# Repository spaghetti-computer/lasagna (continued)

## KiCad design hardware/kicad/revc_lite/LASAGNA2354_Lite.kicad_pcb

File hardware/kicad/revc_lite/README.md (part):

# LASAGNA LITE (WeAct RP2350B), PRE-ROUTE proposal

> **Current configuration (2026-10-17, supersedes everything below).** The Waveshare Core2350B is replaced by the
> **WeAct Studio RP2350B Core Board V1.0** (41.148 x 41.402 mm, two 2x15 2.54 mm headers, rows 38.10 mm apart, own USB-C
> with CC resistors + TVS, BOOT/RST buttons, 16 MB flash). Board stays **100 x 67 mm**. Sections after this one are history
> (Waveshare era) and are kept for reference only. Regenerate with:
>
> `cd ../revc && LASAGNA_LITE=1 python3 gen_sch.py && LASAGNA_LITE=1 python3 gen_pcb.py && LASAGNA_LITE=1 python3 export_fab.py`

## Module (verified against WeActStudio.RP2350BCoreBoard HDK: RP2350B_SCH.pdf H1/H2, RP2350B_PINOUT.png, dimension drawing)
- Footprint `NESPICO_RevC:WeAct_RP2350B_CoreBoard` (generated by `gen_pcb.py` from `design.weact_pins()`): pad 1xx = H1 pin xx, 2xx = H2 pin xx.
  Origin = module centre, +y = USB-C edge. Pin 1/2 row 1.778 mm from the USB edge, far edge 4.064 mm past pin 29/30, rows 38.10 mm (outer) / 33.02 mm (inner) apart.
  The community footprints (fp_leomanes, fp_bwally0) were only used as a cross-check (leomanes agrees within 0.1 mm; bwally0 uses a different pad numbering).
- Placement: module centre (50.00, 46.30), x 29.43-70.57, y 25.60-67.00, **USB-C flush with the front edge**. H2 (GP25-47) on the left, H1 (GP0-24) on the right (top view).
- **H1:** 1 VBUS (raw USB), 2 +5V (after the module diode U2), 3/4 GND, 5 VREF, pin k = GP(k-6) for k = 6..30. Odd = outer row.
- **H2:** 1/2/4 GND, 3 3V3_EN, 5/6 3V3, 7 GP47, 8 RUN, 9 GP45, 10 GP46, 11 GP43, 12 GP44, ... 29 GP25, 30 GP26. Even = outer row.
- **Power:** +5V_LOGIC = **H1-1 VBUS** -> F1 PTC (JP2 bypass, open) -> VBUS_F -> JP1 bridged (D2 SS34 DNP) -> +5V_LOGIC.
  **H1-2 is NOT used**: the module diode drop could take the AHCT supply below 4.5 V. +3V3 = module LDO on H2-5/6.
  Not connected: H1-2 +5V, H1-5 VREF, H2-3 3V3_EN, H2-8 RUN.
- **Module handling (also on the front silk next to the module):**
  - **Lift module R16** (GP23 -> KEY button with a 5.1k pull-up to 3V3). GP23 carries OE#; with R16 fitted a KEY press would enable the AHCT outputs.
  - **Never fit the PSRAM/flash2 footprint U7** on the module bottom (its CS is GP0 = PPU AD0, through R14 0R with R13 10k to 3V3).
  - GP25 (CPU AD0, MCU side of RN1) drives the module LED through 5.1k: harmless (about 0.3 mA), the LED blinks with bus activity.
  - Newer WeAct lots ship RP2350B0**A4** (E9 fixed); R41 (5.1k CIRAM_A10 pull-down) stays fitted anyway (harmless on A4, required on A2).
- Solder the module on the supplied 2x15 male headers (do not fit pins pointing down on its 1x4 SWD header). Only bare THT test pads sit under the module.

## GPIO map (firmware swap, approved 2026-10-17)
| GPIO | Net | Function | Header pin |
|---|---|---|---|
| 0-7 | PADM0-7 | PPU AD0-7 (via RN3/RN4 33R) | H1-6..13 |
| 8-13 | GPA8-13 | PPU A8-13 -> U7 (GPA13 also U8) | H1-14..19 |
| 14 | PPU_DEN_N | U5 245 /OE (R32 10k to 3V3) | H1-20 |
| 15 | G_RD | -> U8 -> CART_RD_N | H1-21 |
| 16 | G_WR_N | U5 DIR, U7 -> CART_WR_N | H1-22 |
| 17 | PPU_ALE | U3 573 LE | H1-23 |
| 18 / 19 / 20 | CVBS_B0 / B1 / B2 | CVBS DAC R90 910 / R91 470 / R92 220 (DNP), 3V3-only | H1-24 / 25 / 26 |
| 21 | IRQ_N | cart pin 15 (R39 10k to 3V3), 5V-tolerant pin | H1-27 |
| 22 | CIRAM_CE_N | cart pin 48, 5V-tolerant pin | H1-28 |
| 23 | OUT_OE_N | OE# of all 7 AHCT (R30 10k to 3V3), 3V3-only. Module KEY pin: **lift R16** | H1-29 |
| 24 | CIRAM_A10 | cart pin 18, **R41 5.1k pull-down** (E9), 5V-tolerant pin | H1-30 |
| 25-32 | CADM0-7 | CPU AD0-7 (via RN1/RN2 33R) | H2-29,30,27,28,25,26,23,24 |
| 33-39 | GA8-14 | CPU A8-14 -> U6 | H2-21,22,19,20,17,18,15 |
| 40 | G_RW | U4 DIR, U6 -> CART_RW | H2-16 |
| 41 | G_ROMSEL_N | U7 -> CART_ROMSEL_N | H2-13 |
| 42 | G_M2_N | U4 /OE, U8 -> M2 (R31 10k to 3V3) | H2-14 |
| 43 | CPU_ALE | U2 573 LE | H2-11 |
| 44 / 45 | I2C_SDA / I2C_SCL | U10 MCP23017, J9 Grove (DNP), 4.7k to 3V3 | H2-12 / H2-9 |
| 46 | SPARE_GP46 | audio PWM (R60, DNP), J10 EXP, TP G46 | H2-10 |
| 47 | SPARE_GP47 | J10 EXP, TP G47 | H2-7 |

- **PIO window rule:** the PPU group (GP0-17) sits inside GPIO0-31 and the CPU group (GP25-43) inside GPIO16-47 (tested).
- **GPIO40-47 rule:** these are the ADC pads and are **not 5 V tolerant**. Every net on GPIO40-47 may only reach an AHCT input
  (573 LE/D, 541/540 A/OE, 245 DIR/OE) or a 3.3 V-only part (MCP23017, Grove, EXP header, 3V3 pull-ups). Never a 245 A/B pin, the cart slot,
  or a pull-up to +5V. `tests/test_lite.py::test_gpio40_47_only_drive_ahct_inputs_or_3v3_parts` enforces it with **zero exceptions**.
  R63 (GPIO46 -> cart pin 45) was deleted 2026-10-17; cart pin 45 (audio from 2A03) is NC again, pin 31 NC (pin 30 = +5V).
  R62 (cart pin 46 -> audio filter, DNP) stays: it only feeds the RC node, never a GPIO directly.
- Firmware order unchanged: set 245 DIR (G_RW / G_WR_N) and the bus levels, then pull the 245 /OE (G_M2_N / PPU_DEN_N) and OE# (GPIO23) low;
  release OE before changing DIR.
- **Lite pin swaps (firmware-invisible):** U2/U3 573 latches carry bit 7-j on D/Q pair j, and each RN 33R array carries bit b0+3-e on element e,
  so the module -> RN -> 573/245 -> slot buses run without crossings.

## Parts changed vs the Waveshare Lite
- **Removed:** J1 Akizuki USB-C breakout, R5/R6 CC 5.1k, U12 USBLC6-2SC6 (the module has USB-C, CC and TVS), SW1/SW2 (module has BOOT/RST),
  TP SWC/SWD/BT/RUN, the "DO NOT USE MODULE FPC" silk. The 22nd TP is GND again.
- **Changed:** U1 = WeAct RP2350B (60 pins, new symbol/footprint, courtyard 41.65 x 41.65 mm, silk on 3 sides, fab marks for the RP2350B, PSRAM U7, SWD 1x4 and USB-C shell legs).
  F1 now fed from H1-1 VBUS. GPIO map as above. R41 moved with CIRAM_A10 (GP24).
- **Kept:** F1 PTC (fitted) + JP2 (open), D2 SS34 DNP + JP1 bridged, R30/R31/R32/R39 pull-ups to 3V3, R41 5.1k fitted, all DNP options
  (MCP23017 + J4/J5, Grove J9 Seeed order, CVBS + J6, audio chain + J11, J10 EXP).

## Placement (mm, board origin top-left, y down; all key parts locked)
| Part | Position | Note |
|---|---|---|
| J3 cart slot | pin 1 (13.17, 7.80) | top edge, CPU pins left, PPU right |
| Row A, y = 18.0, 13 mm pitch | U6 11.0 (90), U2 24.0 (90), U4 37.0 (270), U8 50.0 (90), U7 63.0 (90), U3 76.0 (90), U5 89.0 (270) | inputs face the module, outputs face the slot (245 A side up) |
| 100 nF | C14 (8.08,12.54) C10 (21.08,12.54) C12 (39.93,23.46) C16 (47.07,12.54) C15 (60.07,12.54) C11 (73.07,12.54) C13 (91.93,23.46) | 2.6 mm from each VCC pin 20 |
| Pull-ups in row-A gaps | R31 (42.3,18) R30 (44.7,18) R39 (55.3,18) R41 (57.7,18) R32 (69.5,18) | on G_M2_N / OE# / IRQ / A10 / DEN |
| U1 WeAct | centre (50.00, 46.30) | USB-C flush with y = 67 |
| RN1 / RN2 | (26.4, 31.0) / (26.4, 36.0), 180 deg | left of H2 GP25-32 |
| RN3 / RN4 | (73.6, 57.1) / (73.6, 52.5), 0 deg | right of H1 GP0-7 |
| F1 / JP2 / D2 / JP1 / C1 | (74.6,64.8) / (74.6,61.6) / (80.6,64.8) / (80.6,61.6) / (86.0,64.8) | next to H1-1 VBUS, two aligned columns + C1 on the same row |
| TP1-22 | 3 rows (y 27.0 / 30.9 / 34.8) x 8, 3.2 mm pitch, centred x = 48.5 | bare THT pads under the module's far end, labels on B.Silk |
| CVBS / audio passives | R90/R91/R92 (80.4/82.0/84.0, 35.0); R60/C60/C61 (same x, 45.0); R61/R62 (80.4/82.0, 50.0) | one column grid per RCA |
| Options | J6 (93.1,33) J11 (93.1,49) right edge; J9 (6,52) U10 (16.6,51.4) J10 (24.6,46.4) J12 RST (24.6,40.0) J5 (11.9,60.9) J4 (11.9,64.8) left | all DNP |

Routing intent for Quilter: CPU signals leave H2 to the left (CAD via RN1/RN2 straight up to U2/U4, GA8-14/G_RW left then up to U6);
G_ROMSEL_N / G_M2_N / CPU_ALE and the PPU A8-13 / WR / RD lines may use the lanes under the module beside the TP block; PAD via RN3/RN4 up the
right side to U3/U5; IRQ/CIRAM lines from the top of H1 straight up to the slot centre. Nothing but flat test pads sits under the module.

## Cost change vs the Waveshare Lite (estimate, 1 USD = 150 JPY)
- Module: WeAct RP2350B about $4.2 + shipping (AliExpress; includes 2x 30-pin and SWD headers) vs Core2350B ¥1,463 (Switch Science kit) / $4.9-7.99: about -¥0 to -¥800.
- Removed: Akizuki J1 breakout -¥180, U12 USBLC6 MOQ 10 -¥72, Akizuki 1x40 header strips -¥70 (headers come with the module). R5/R6 were the same 5.1k line as R41 (no saving).
- **Net: about -¥320 on parts, up to about -¥1,100 including the module.** PCB price unchanged (same 100 x 67 mm, 2 layers).

## Population: Lite build vs Full build
The minimal build is a fully working dump-only Lite: every option footprint may stay empty (tested in `LitePopulationTest`:
no logic-IC pin floats without the options, +5V reaches the logic through F1 + bridged JP1).

| Function | Lite build (fit) | Full build (additionally fit) |
|---|---|---|
| MCU | U1 WeAct RP2350B (R16 lifted, no PSRAM) | same |
| Power | F1 PTC, JP1 bridged, C1, JP2 open | D2 SS34 (then cut JP1) only if back-feed protection wanted |
| Cart bus | J3 slot, U2/U3 573, U4/U5 245, U6/U7 541, U8 540, C10-C16, RN1-RN4 33R | same |
| Pulls | R30, R31, R32, R39 (3V3), R41 5.1k (E9) | same |
| Controller pads | - | U10 MCP23017, C27, R51-R53, R42/R43, J4 PAD1, J5 PAD2 |
| Grove I2C | - | J9 (shares U10's I2C, GP44/45) |
| Video | - | R90-R92 DAC, J6 RCA (GP18-20) |
| Audio | - | R60, C60, C61, R61, J11 RCA (GP46 PWM); R62 to mix cart audio (pin 46) |
| Expansion | - | J10 EXP (3V3, GP46, GP47, GND, 5V) |
| Reset/boot | module RST/BOOT buttons | J12 RST header (RUN to GND) for a case button |
| Test | TP1-22 (bare pads) | same |

Rev.C features without a footprint now: USB-C/CC/ESD, SW1/SW2 buttons and SWD header (all on the module: its USB-C, RST/BOOT
buttons and SWD 1x4), crystal and flash (on the module). Nothing else is missing; J12 was added (DNP) for an external reset.

## Checks (2026-10-17)
- `python3 -m pytest tests`: 81 passed (incl. golden netlist, ERC, GPIO40-47 rule with zero exceptions, PIO windows, population test, H1-2 / 3V3_EN unused, 3V3 pull-ups).
- ERC 0 errors / 0 warnings. DRC with schematic parity: 0 violations, 0 footprint errors, 283 unconnected (unrouted, expected).
- Fitted JLC BOM: 10 lines, 25 SMD placements (U1/J3 and DNP options hand-assembled).

---

# History (Waveshare Core2350B era, superseded)

> **Current configuration (2026-10-13 21:50, supersedes older notes below):** bare Core2350B0 (no kit/FPC adapter needed);
> USB-C = Akizuki 115426 breakout J1 + R5/R6 5.1k; VBUS = +5V_LOGIC = module VBUS = cart 5V (no PTC, no ESD, no cart power switch);
> 33R = RN1-RN4 (C25508); pulls R30 OE#, R31 G_M2_N, R32 PPU_DEN_N, R39 IRQ_N all to **3V3**; R41 **5.1k fitted** (E9: Waveshare photo shows RP2350B0A2).
> VBUS: J1 pin1 (VBUS_IN) -> **D2 SS34** (C8678, Basic) -> +5V_LOGIC; **JP1** normally-open solder jumper 'SHORT=BYPASS D' across D2.
> Board **100 x 67 mm** (DNP option row added). Full-version features are DNP footprints (table at the end). Do **not** connect the module FPC while J1 is used (both feed VBUS). Unplug USB before swapping carts.
> Firmware order: set 245 DIR (G_RW / G_WR_N) and the address/data levels first, then pull the 245 OE (G_M2_N / PPU_DEN_N) and OE# (GPIO43) low;
> release OE before changing DIR. Never drive GPIO39 (CIRAM_CE_N). Sections below are history.

This is the Rev.C cart circuit with the bare RP2354B and its support parts replaced by a **Waveshare Core2350B** module (RP2350B, 16 MB flash, 12 MHz crystal, ME6217 3.3 V/800 mA LDO, 27 Ω USB resistors on the module).
It is generated from `../revc/*.py` with `LASAGNA_LITE=1`; Rev.C itself is not changed:

```
cd ../revc && LASAGNA_LITE=1 python3 gen_sch.py && LASAGNA_LITE=1 python3 gen_pcb.py && LASAGNA_LITE=1 python3 export_fab.py
```

Board: 100 × 62 mm (same as Rev.C), 2 layers, black mask, M3 holes at the corners. It is within JLC's ≤100×100 mm cheapest price tier, so making it smaller would not lower the price.
Assembly is all hand-soldered by default (TSSOP-20, 0603/0805, SOT-23). PCBA is not required.

## Module (verified against the Waveshare sources)
- **Outline:** Core2350B0 wiki size drawing. 25.40 mm square, 64 THT pads on a 10×10 grid at 2.54 mm pitch, two pads deep around the edge (pad grid span 22.86 mm).
- **Pinout:** `Core2350B.pdf`, P1–P4 "Header 8X2".
  - P1 (left): GPIO0–14
  - P3 (bottom): GPIO15–29
  - P4 (right): GPIO30–44
  - P2 (top): 1 GND, 2 GP45, 3 GP47 (through R11 0R), 4 GP46, 5 BOOTSEL, 6 SWD, 7 USBD_N, 8 GND, 9 USBD_P, 10 SWCLK, 11 RUN, 12 ADC_VREF, 13 3V3_EN, 14 GND, 15 VBUS, 16 3V3
  - Footprint pad number = header × 100 + pin.
- **Mounting:** solder the module to male 2.54 mm headers (Akizuki 1×40 strips cut to length), or solder it flat.

## What changed from Rev.C
- **Removed:**
  - U1 and its support: L1, Y1, C5–C9, R1, R2, the C17–C24 / C28–C32 decoupling, R3, R4, R7, R8.
  - U9 NCP1117 and C2. The module LDO supplies +3V3, and the load is well under the LDO's rating (the AHCT logic runs from 5 V).
  - D1 and its 1k (the module LED is enough), the CVBS DAC/RCA, MCP23017/Grove/pad headers, and the J7 SWD header (SWCLK/SWDIO are on the test-point row instead).
- **USB-C:** CC 5.1k ×2, then F1 → +5V_LOGIC → module VBUS (P2-15). D+/D− go straight to P2-9/P2-7, because the 27 Ω resistors are on the module.
- **Kept:** U11 power-down guard, on the module's 3V3.
- **SW1/SW2:** **optional**. A blank flash enumerates as USB BOOTSEL by itself; the module has no buttons of its own.
- **GPIO map unchanged** (same firmware as Rev.C).
  - GPIO39 (module red LED, 470 Ω) is CIRAM_CE_N, an input that the cart drives. The LED loads it by about 7 mA. **Firmware must never drive GPIO39.** **Remove the module's R10 (recommended)**: CIRAM /CE is often PPU /A13 driven by U8 or the cart, and the LED would load it.
  - GPIO40–42/44/45 (unused CVBS/I2C) and **GPIO47 are not connected**, so the B1/B2 variants (with PSRAM) also work. B0 is recommended.
- **Clock:** the module is rated for 150 MHz. The 172 MHz overclock is the same silicon, but it is unverified on the module.

## Cost (1 board, cheapest; 1 USD = 150 JPY)
| Item | Cost | Source |
|---|---|---|
| PCB, 5 boards | $2–4 (¥300–600) | estimate |
| Shipping, PCB + LCSC parts together, cheapest service | $8–15 (¥1,200–2,250) | estimate |
| Parts (LCSC/JLC unit prices incl. LCSC minimum order quantities) | about $11.1 (¥1,670), of which ICs $4.44 | JLC API prices from 2026-10-13 |
| Core2350B module | ¥1,463 (Switch Science B2-Kit) / $4.9 (SpotPear B0, plus shipping) / $7.99 (Waveshare) | fetched |
| Pin headers, 1×40 ×2 (Akizuki 100167) | ¥70 | fetched |
| J3 Hirose slot | ¥0 (already owned) | |
| Consumption tax | ¥0 (personal-import taxable base under ¥10,000) | estimate |
| **Total** | **about ¥4,700–6,300** | |

Optional:
- SW1/SW2 TS-1187A: about ¥15 including MOQ.
- JLC Basic PCBA (16 lines): about +$12 (setup $8, stencil $1.5, parts).

The leftover MOQ parts (5–100 pcs per line) cover 2 or more more boards. With a second module and a second slot, an extra board costs about ¥2,000–3,500.

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
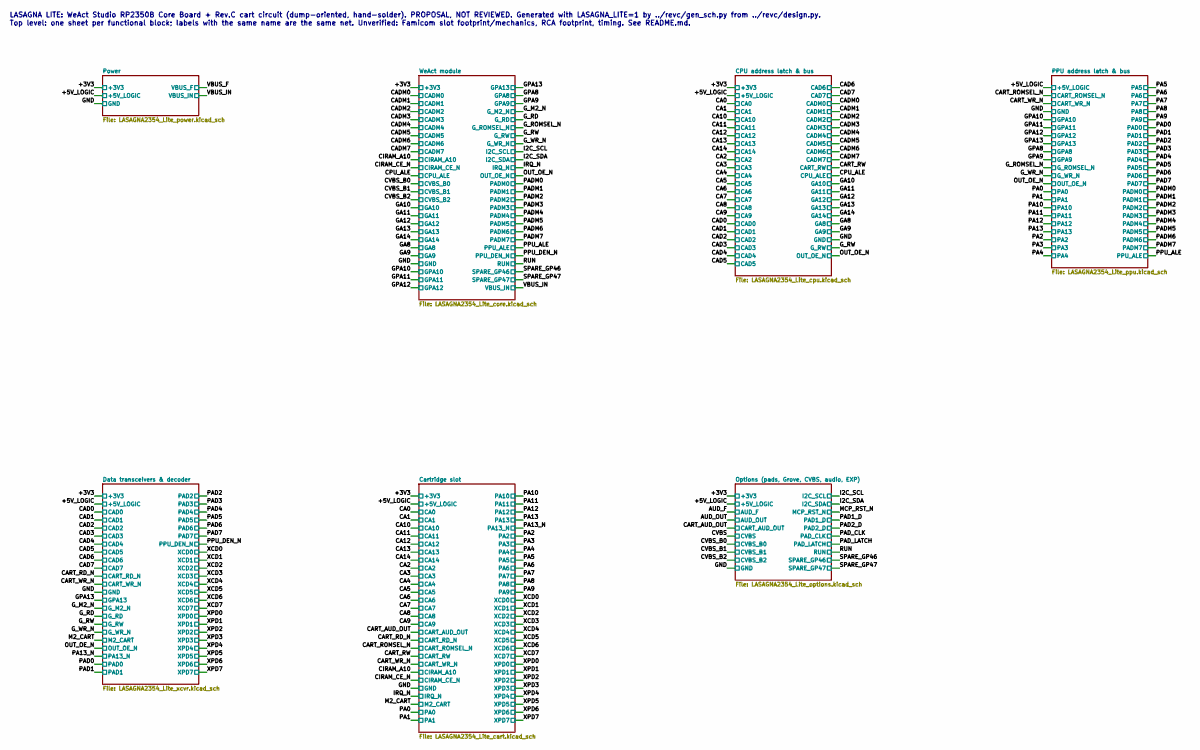
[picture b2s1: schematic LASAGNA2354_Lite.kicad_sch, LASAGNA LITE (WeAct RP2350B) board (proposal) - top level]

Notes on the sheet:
LASAGNA LITE: WeAct Studio RP2350B Core Board + Rev.C cart circuit (dump-oriented, hand-solder). PROPOSAL, NOT REVIEWED. Generated with LASAGNA_LITE=1 by ../revc/gen_sch.py from ../revc/design.py. Top level: one sheet per functional block; labels with the same name are the same net. Unverified: Fam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

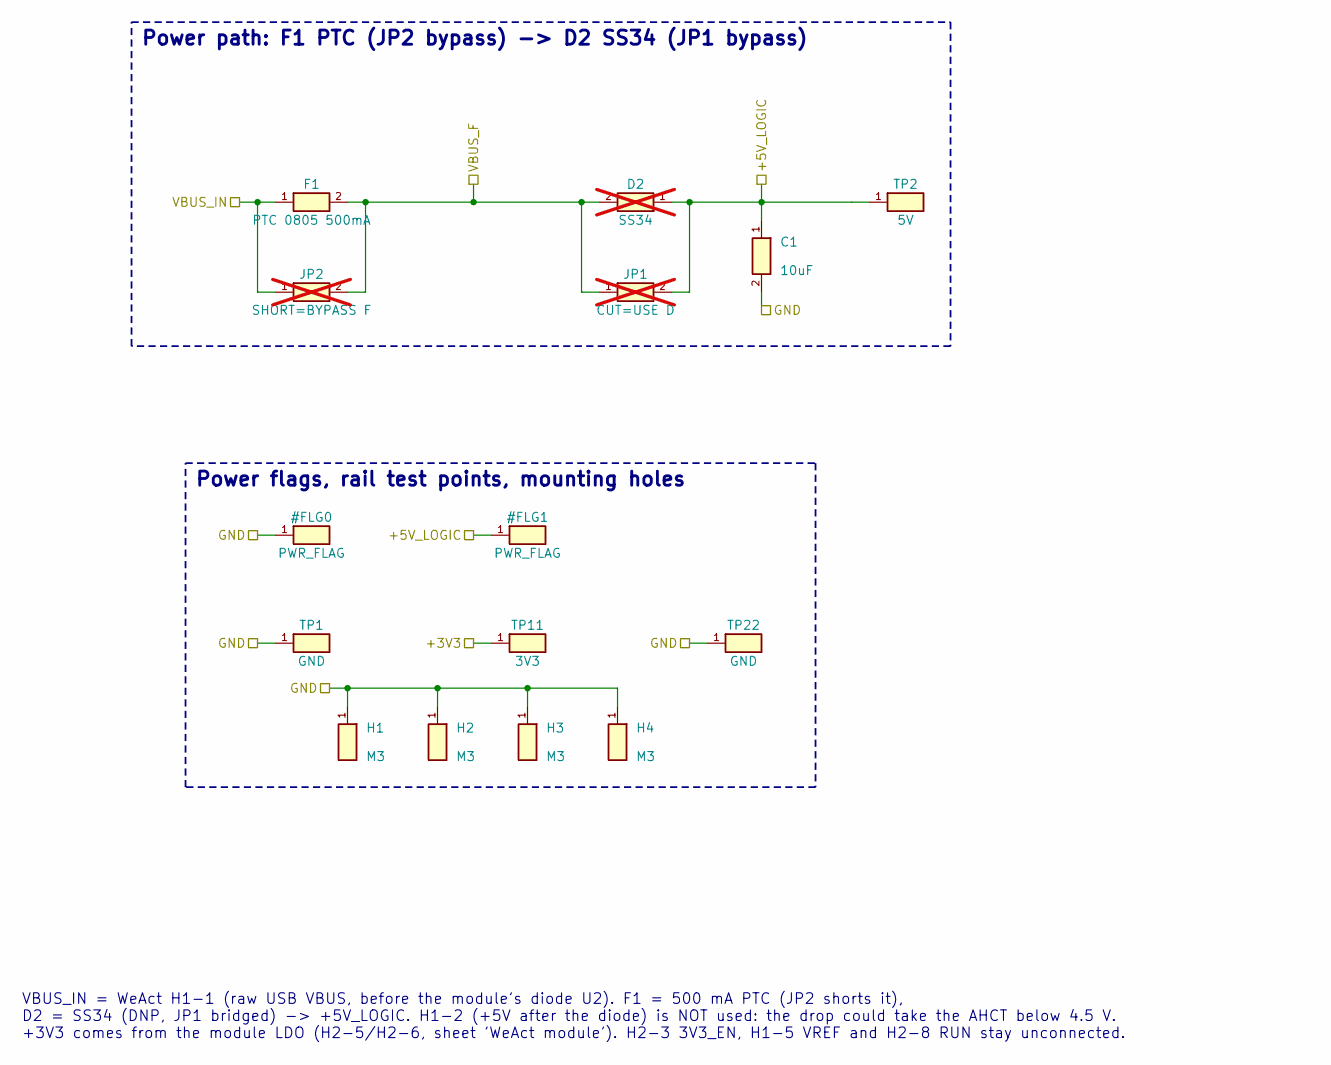
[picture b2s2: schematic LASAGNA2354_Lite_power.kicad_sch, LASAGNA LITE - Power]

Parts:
C1: 10uF; C_0805_2012Metric; MPN 10uF; LCSC C15850
D2: SS34; D_SMA; MPN SS34; LCSC C8678; not fitted
F1: PTC 0805 500mA; Fuse_0805_2012Metric; MPN SMD0805-050; LCSC C66452
H1, H2, H3, H4: M3; MountingHole_3.2mm_M3_Pad; LCSC_Status no LCSC part
JP1: CUT=USE D; SolderJumper-2_P1.3mm_Bridged_RoundedPad1.0x1.5mm; LCSC_Status hand-assembly / not PCBA; not fitted
JP2: SHORT=BYPASS F; SolderJumper-2_P1.3mm_Open_RoundedPad1.0x1.5mm; LCSC_Status hand-assembly / not PCBA; not fitted
TP1, TP22: GND; TestPoint_THTPad_D2.0mm_Drill1.0mm; LCSC_Status no LCSC part
TP2: 5V; TestPoint_THTPad_D2.0mm_Drill1.0mm; LCSC_Status no LCSC part
TP11: 3V3; TestPoint_THTPad_D2.0mm_Drill1.0mm; LCSC_Status no LCSC part

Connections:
/+3V3: TP11.1; also elsewhere on the board
/+5V_LOGIC: C1.1, D2.1 (K), JP1.2, TP2.1; also elsewhere on the board
/GND: C1.2, H1.1, H2.1, H3.1, H4.1, TP1.1, TP22.1; also elsewhere on the board
/VBUS_F: D2.2 (A), F1.2, JP1.1, JP2.2
/VBUS_IN: F1.1, JP2.1; also elsewhere on the board

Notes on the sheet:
VBUS_IN = WeAct H1-1 (raw USB VBUS, before the module's diode U2). F1 = 500 mA PTC (JP2 shorts it), D2 = SS34 (DNP, JP1 bridged) -> +5V_LOGIC. H1-2 (+5V after the diode) is NOT used: the drop could take the AHCT below 4.5 V. +3V3 comes from the module LDO (H2-5/H2-6, sheet 'WeAct module'). H2-3 3V3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
Power path: F1 PTC (JP2 bypass) -> D2 SS34 (JP1 bypass)
Power flags, rail test points, mounting holes

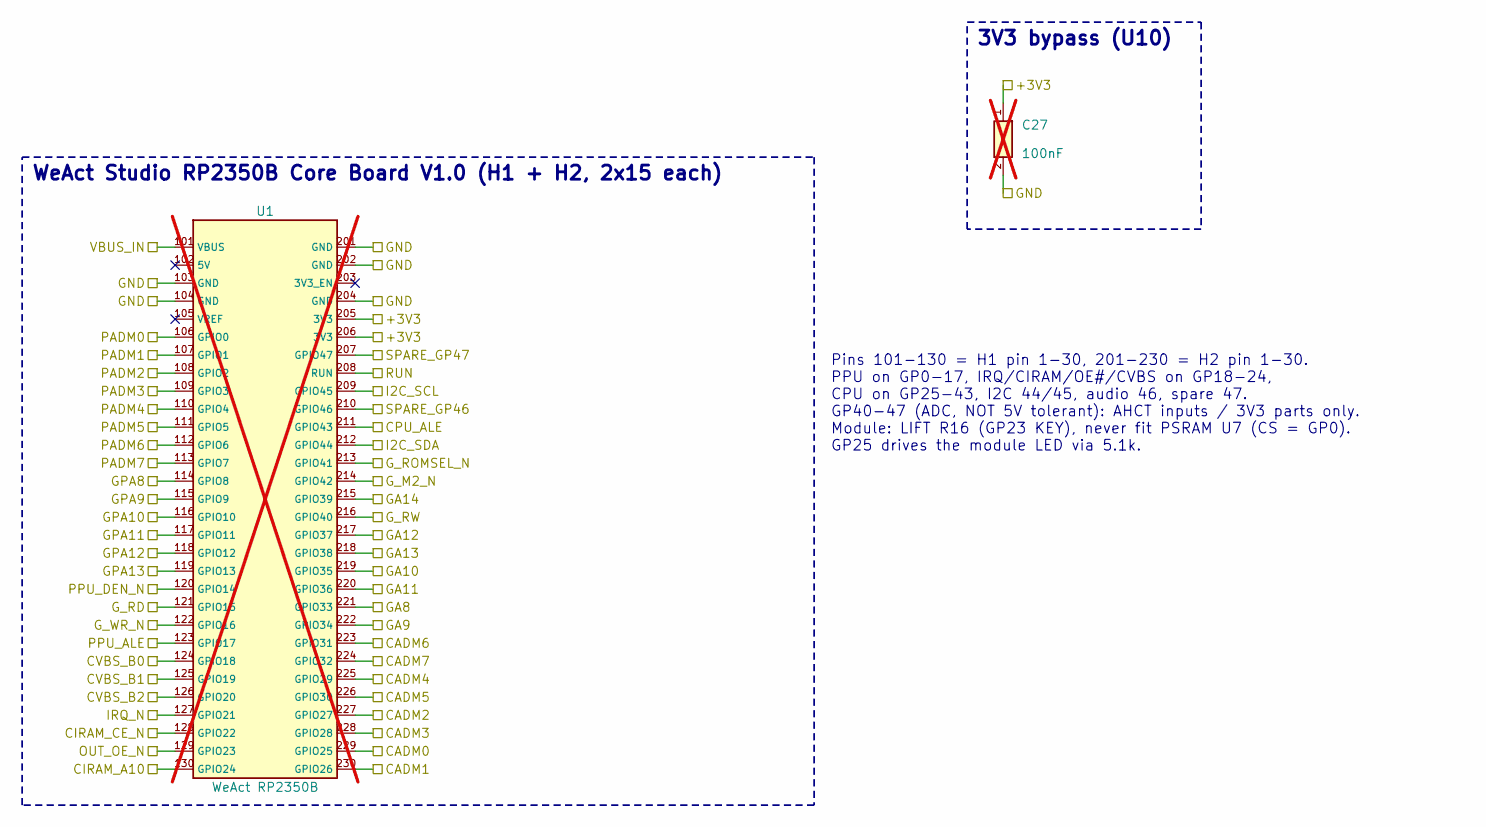
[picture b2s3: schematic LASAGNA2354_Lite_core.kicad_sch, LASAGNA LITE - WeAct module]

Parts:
C27: 100nF; C_0603_1608Metric; MPN 100nF; LCSC C14663; not fitted
U1: WeAct RP2350B; WeAct_RP2350B_CoreBoard; MPN WeAct RP2350B Core Board V1.0; LCSC_Status hand-assembly / not PCBA; not fitted

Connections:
/+3V3: C27.1, U1.205 (3V3), U1.206 (3V3); also elsewhere on the board
/CADM0: U1.229 (GPIO25); also elsewhere on the board
/CADM1: U1.230 (GPIO26); also elsewhere on the board
/CADM2: U1.227 (GPIO27); also elsewhere on the board
/CADM3: U1.228 (GPIO28); also elsewhere on the board
/CADM4: U1.225 (GPIO29); also elsewhere on the board
/CADM5: U1.226 (GPIO30); also elsewhere on the board
/CADM6: U1.223 (GPIO31); also elsewhere on the board
/CADM7: U1.224 (GPIO32); also elsewhere on the board
/CIRAM_A10: U1.130 (GPIO24); also elsewhere on the board
/CIRAM_CE_N: U1.128 (GPIO22); also elsewhere on the board
/CPU_ALE: U1.211 (GPIO43); also elsewhere on the board
/CVBS_B0: U1.124 (GPIO18); also elsewhere on the board
/CVBS_B1: U1.125 (GPIO19); also elsewhere on the board
/CVBS_B2: U1.126 (GPIO20); also elsewhere on the board
/GA8: U1.221 (GPIO33); also elsewhere on the board
/GA9: U1.222 (GPIO34); also elsewhere on the board
/GA10: U1.219 (GPIO35); also elsewhere on the board
/GA11: U1.220 (GPIO36); also elsewhere on the board
/GA12: U1.217 (GPIO37); also elsewhere on the board
/GA13: U1.218 (GPIO38); also elsewhere on the board
/GA14: U1.215 (GPIO39); also elsewhere on the board
/GND: C27.2, U1.103 (GND), U1.104 (GND), U1.201 (GND), U1.202 (GND), U1.204 (GND); also elsewhere on the board
/GPA8: U1.114 (GPIO8); also elsewhere on the board
/GPA9: U1.115 (GPIO9); also elsewhere on the board
/GPA10: U1.116 (GPIO10); also elsewhere on the board
/GPA11: U1.117 (GPIO11); also elsewhere on the board
/GPA12: U1.118 (GPIO12); also elsewhere on the board
/GPA13: U1.119 (GPIO13); also elsewhere on the board
/G_M2_N: U1.214 (GPIO42); also elsewhere on the board
/G_RD: U1.121 (GPIO15); also elsewhere on the board
/G_ROMSEL_N: U1.213 (GPIO41); also elsewhere on the board
/G_RW: U1.216 (GPIO40); also elsewhere on the board
/G_WR_N: U1.122 (GPIO16); also elsewhere on the board
/I2C_SCL: U1.209 (GPIO45); also elsewhere on the board
/I2C_SDA: U1.212 (GPIO44); also elsewhere on the board
/IRQ_N: U1.127 (GPIO21); also elsewhere on the board
/OUT_OE_N: U1.129 (GPIO23); also elsewhere on the board
/PADM0: U1.106 (GPIO0); also elsewhere on the board
/PADM1: U1.107 (GPIO1); also elsewhere on the board
/PADM2: U1.108 (GPIO2); also elsewhere on the board
/PADM3: U1.109 (GPIO3); also elsewhere on the board
/PADM4: U1.110 (GPIO4); also elsewhere on the board
/PADM5: U1.111 (GPIO5); also elsewhere on the board
/PADM6: U1.112 (GPIO6); also elsewhere on the board
/PADM7: U1.113 (GPIO7); also elsewhere on the board
/PPU_ALE: U1.123 (GPIO17); also elsewhere on the board
/PPU_DEN_N: U1.120 (GPIO14); also elsewhere on the board
/RUN: U1.208 (RUN); also elsewhere on the board
/SPARE_GP46: U1.210 (GPIO46); also elsewhere on the board
/SPARE_GP47: U1.207 (GPIO47); also elsewhere on the board
/VBUS_IN: U1.101 (VBUS); also elsewhere on the board

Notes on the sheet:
Pins 101-130 = H1 pin 1-30, 201-230 = H2 pin 1-30. PPU on GP0-17, IRQ/CIRAM/OE#/CVBS on GP18-24, CPU on GP25-43, I2C 44/45, audio 46, spare 47. GP40-47 (ADC, NOT 5V tolerant): AHCT inputs / 3V3 parts only. Module: LIFT R16 (GP23 KEY), never fit PSRAM U7 (CS = GP0). GP25 drives the module LED via 5.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
WeAct Studio RP2350B Core Board V1.0 (H1 + H2, 2x15 each)
3V3 bypass (U10)

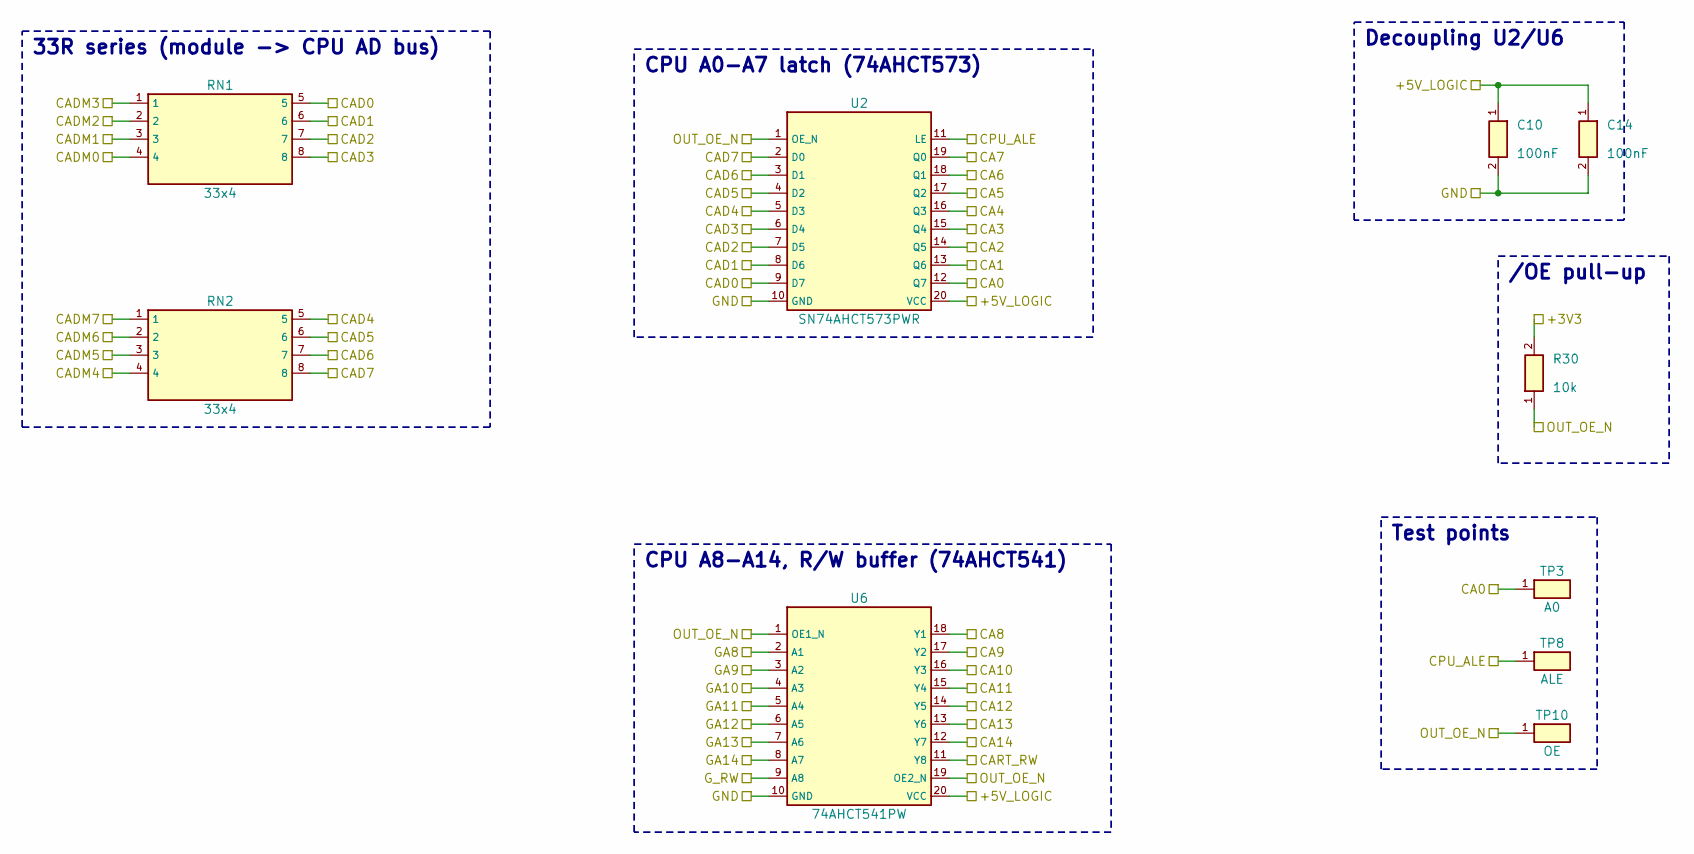
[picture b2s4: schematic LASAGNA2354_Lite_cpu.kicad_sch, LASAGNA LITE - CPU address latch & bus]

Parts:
C10, C14: 100nF; C_0603_1608Metric; MPN 100nF; LCSC C14663
R30: 10k; R_0603_1608Metric; MPN 10k; LCSC C25804
RN1, RN2: 33x4; R_Array_Convex_4x0603; MPN 4D03WGJ0330T5E; LCSC C25508
TP3: A0; TestPoint_THTPad_D2.0mm_Drill1.0mm; LCSC_Status no LCSC part
TP8: ALE; TestPoint_THTPad_D2.0mm_Drill1.0mm; LCSC_Status no LCSC part
TP10: OE; TestPoint_THTPad_D2.0mm_Drill1.0mm; LCSC_Status no LCSC part
U2: SN74AHCT573PWR; TSSOP-20_4.4x6.5mm_P0.65mm; MPN SN74AHCT573PWR; LCSC C141311
U6: 74AHCT541PW; TSSOP-20_4.4x6.5mm_P0.65mm; MPN 74AHCT541PW,118; LCSC C84548

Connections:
/+3V3: R30.2; also elsewhere on the board
/+5V_LOGIC: C10.1, C14.1, U2.20 (VCC), U6.20 (VCC); also elsewhere on the board
/CA0: TP3.1, U2.12 (Q7); also elsewhere on the board
/CA1: U2.13 (Q6); also elsewhere on the board
/CA2: U2.14 (Q5); also elsewhere on the board
/CA3: U2.15 (Q4); also elsewhere on the board
/CA4: U2.16 (Q3); also elsewhere on the board
/CA5: U2.17 (Q2); also elsewhere on the board
/CA6: U2.18 (Q1); also elsewhere on the board
/CA7: U2.19 (Q0); also elsewhere on the board
/CA8: U6.18 (Y1); also elsewhere on the board
/CA9: U6.17 (Y2); also elsewhere on the board
/CA10: U6.16 (Y3); also elsewhere on the board
/CA11: U6.15 (Y4); also elsewhere on the board
/CA12: U6.14 (Y5); also elsewhere on the board
/CA13: U6.13 (Y6); also elsewhere on the board
/CA14: U6.12 (Y7); also elsewhere on the board
/CAD0: RN1.5, U2.9 (D7); also elsewhere on the board
/CAD1: RN1.6, U2.8 (D6); also elsewhere on the board
/CAD2: RN1.7, U2.7 (D5); also elsewhere on the board
/CAD3: RN1.8, U2.6 (D4); also elsewhere on the board
/CAD4: RN2.5, U2.5 (D3); also elsewhere on the board
/CAD5: RN2.6, U2.4 (D2); also elsewhere on the board
/CAD6: RN2.7, U2.3 (D1); also elsewhere on the board
/CAD7: RN2.8, U2.2 (D0); also elsewhere on the board
/CADM0: RN1.4; also elsewhere on the board
/CADM1: RN1.3; also elsewhere on the board
/CADM2: RN1.2; also elsewhere on the board
/CADM3: RN1.1; also elsewhere on the board
/CADM4: RN2.4; also elsewhere on the board
/CADM5: RN2.3; also elsewhere on the board
/CADM6: RN2.2; also elsewhere on the board
/CADM7: RN2.1; also elsewhere on the board
/CART_RW: U6.11 (Y8); also elsewhere on the board
/CPU_ALE: TP8.1, U2.11 (LE); also elsewhere on the board
/GA8: U6.2 (A1); also elsewhere on the board
/GA9: U6.3 (A2); also elsewhere on the board
/GA10: U6.4 (A3); also elsewhere on the board
/GA11: U6.5 (A4); also elsewhere on the board
/GA12: U6.6 (A5); also elsewhere on the board
/GA13: U6.7 (A6); also elsewhere on the board
/GA14: U6.8 (A7); also elsewhere on the board
/GND: C10.2, C14.2, U2.10 (GND), U6.10 (GND); also elsewhere on the board
/G_RW: U6.9 (A8); also elsewhere on the board
/OUT_OE_N: R30.1, TP10.1, U2.1 (OE_N), U6.1 (OE1_N), U6.19 (OE2_N); also elsewhere on the board

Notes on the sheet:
33R series (module -> CPU AD bus)
CPU A0-A7 latch (74AHCT573)
CPU A8-A14, R/W buffer (74AHCT541)
Decoupling U2/U6
/OE pull-up
Test points

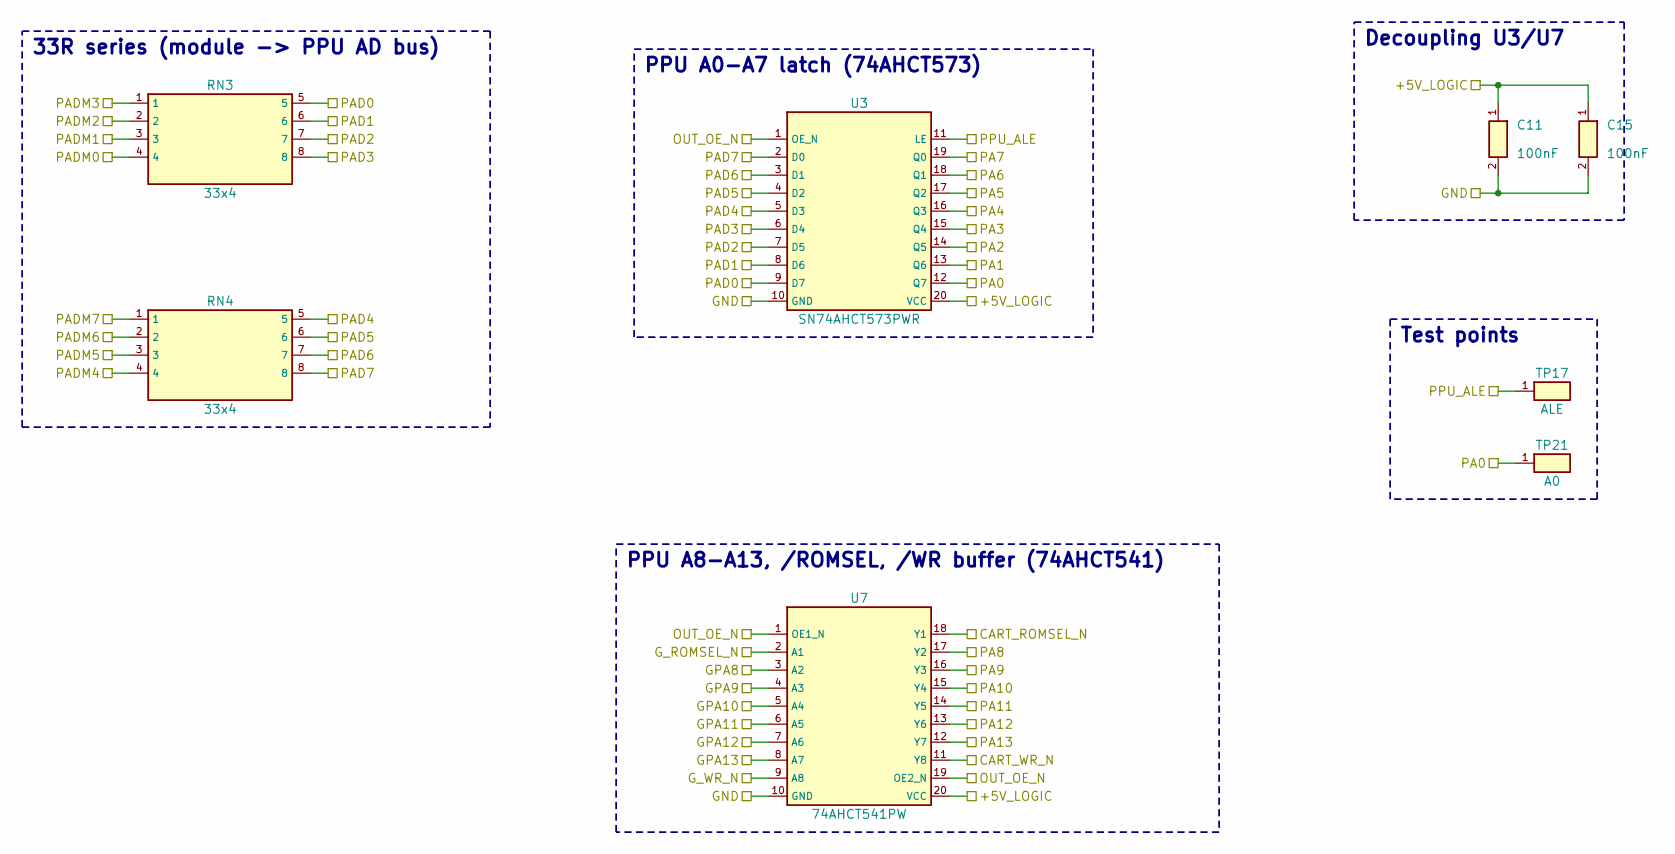
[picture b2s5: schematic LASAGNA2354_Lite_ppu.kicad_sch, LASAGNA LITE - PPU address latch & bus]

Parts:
C11, C15: 100nF; C_0603_1608Metric; MPN 100nF; LCSC C14663
RN3, RN4: 33x4; R_Array_Convex_4x0603; MPN 4D03WGJ0330T5E; LCSC C25508
TP17: ALE; TestPoint_THTPad_D2.0mm_Drill1.0mm; LCSC_Status no LCSC part
TP21: A0; TestPoint_THTPad_D2.0mm_Drill1.0mm; LCSC_Status no LCSC part
U3: SN74AHCT573PWR; TSSOP-20_4.4x6.5mm_P0.65mm; MPN SN74AHCT573PWR; LCSC C141311
U7: 74AHCT541PW; TSSOP-20_4.4x6.5mm_P0.65mm; MPN 74AHCT541PW,118; LCSC C84548

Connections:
/+5V_LOGIC: C11.1, C15.1, U3.20 (VCC), U7.20 (VCC); also elsewhere on the board
/CART_ROMSEL_N: U7.18 (Y1); also elsewhere on the board
/CART_WR_N: U7.11 (Y8); also elsewhere on the board
/GND: C11.2, C15.2, U3.10 (GND), U7.10 (GND); also elsewhere on the board
/GPA8: U7.3 (A2); also elsewhere on the board
/GPA9: U7.4 (A3); also elsewhere on the board
/GPA10: U7.5 (A4); also elsewhere on the board
/GPA11: U7.6 (A5); also elsewhere on the board
/GPA12: U7.7 (A6); also elsewhere on the board
/GPA13: U7.8 (A7); also elsewhere on the board
/G_ROMSEL_N: U7.2 (A1); also elsewhere on the board
/G_WR_N: U7.9 (A8); also elsewhere on the board
/OUT_OE_N: U3.1 (OE_N), U7.1 (OE1_N), U7.19 (OE2_N); also elsewhere on the board
/PA0: TP21.1, U3.12 (Q7); also elsewhere on the board
/PA1: U3.13 (Q6); also elsewhere on the board
/PA2: U3.14 (Q5); also elsewhere on the board
/PA3: U3.15 (Q4); also elsewhere on the board
/PA4: U3.16 (Q3); also elsewhere on the board
/PA5: U3.17 (Q2); also elsewhere on the board
/PA6: U3.18 (Q1); also elsewhere on the board
/PA7: U3.19 (Q0); also elsewhere on the board
/PA8: U7.17 (Y2); also elsewhere on the board
/PA9: U7.16 (Y3); also elsewhere on the board
/PA10: U7.15 (Y4); also elsewhere on the board
/PA11: U7.14 (Y5); also elsewhere on the board
/PA12: U7.13 (Y6); also elsewhere on the board
/PA13: U7.12 (Y7); also elsewhere on the board
/PAD0: RN3.5, U3.9 (D7); also elsewhere on the board
/PAD1: RN3.6, U3.8 (D6); also elsewhere on the board
/PAD2: RN3.7, U3.7 (D5); also elsewhere on the board
/PAD3: RN3.8, U3.6 (D4); also elsewhere on the board
/PAD4: RN4.5, U3.5 (D3); also elsewhere on the board
/PAD5: RN4.6, U3.4 (D2); also elsewhere on the board
/PAD6: RN4.7, U3.3 (D1); also elsewhere on the board
/PAD7: RN4.8, U3.2 (D0); also elsewhere on the board
/PADM0: RN3.4; also elsewhere on the board
/PADM1: RN3.3; also elsewhere on the board
/PADM2: RN3.2; also elsewhere on the board
/PADM3: RN3.1; also elsewhere on the board
/PADM4: RN4.4; also elsewhere on the board
/PADM5: RN4.3; also elsewhere on the board
/PADM6: RN4.2; also elsewhere on the board
/PADM7: RN4.1; also elsewhere on the board
/PPU_ALE: TP17.1, U3.11 (LE); also elsewhere on the board

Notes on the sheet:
33R series (module -> PPU AD bus)
PPU A0-A7 latch (74AHCT573)
PPU A8-A13, /ROMSEL, /WR buffer (74AHCT541)
Decoupling U3/U7
Test points

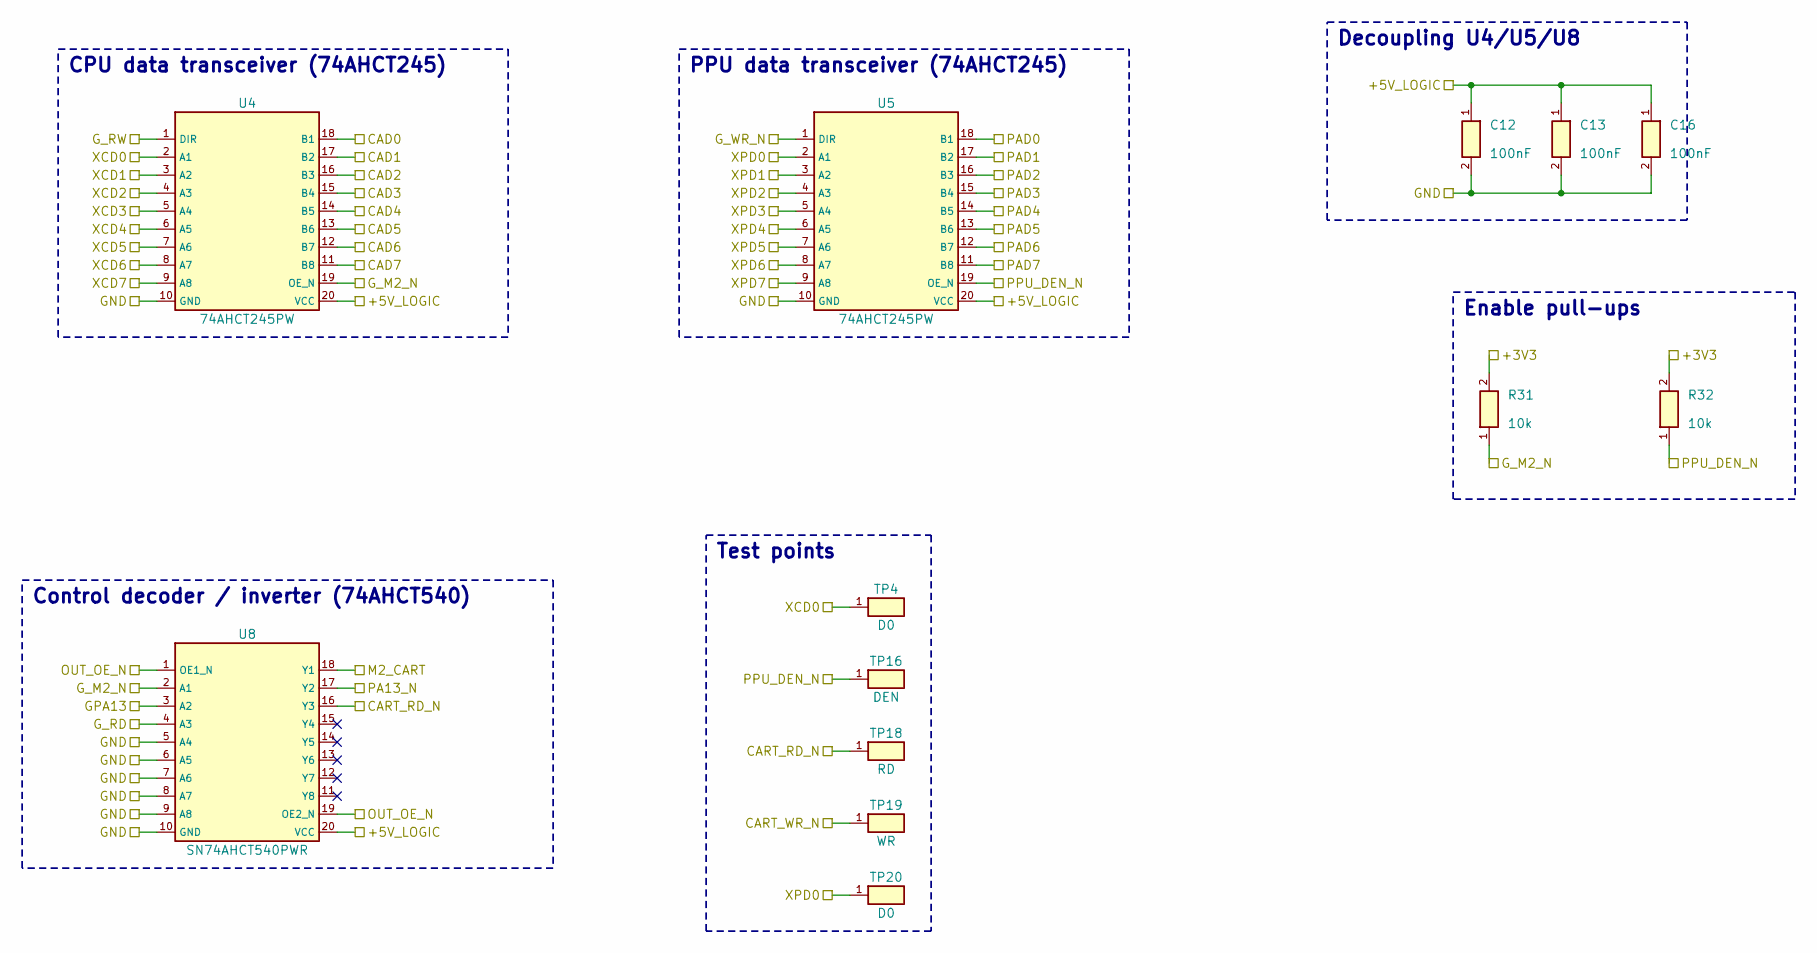
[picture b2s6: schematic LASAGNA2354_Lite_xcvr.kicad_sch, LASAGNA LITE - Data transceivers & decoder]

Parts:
C12, C13, C16: 100nF; C_0603_1608Metric; MPN 100nF; LCSC C14663
R31, R32: 10k; R_0603_1608Metric; MPN 10k; LCSC C25804
TP4, TP20: D0; TestPoint_THTPad_D2.0mm_Drill1.0mm; LCSC_Status no LCSC part
TP16: DEN; TestPoint_THTPad_D2.0mm_Drill1.0mm; LCSC_Status no LCSC part
TP18: RD; TestPoint_THTPad_D2.0mm_Drill1.0mm; LCSC_Status no LCSC part
TP19: WR; TestPoint_THTPad_D2.0mm_Drill1.0mm; LCSC_Status no LCSC part
U4, U5: 74AHCT245PW; TSSOP-20_4.4x6.5mm_P0.65mm; MPN 74AHCT245PW,118; LCSC C173388
U8: SN74AHCT540PWR; TSSOP-20_4.4x6.5mm_P0.65mm; MPN SN74AHCT540PWR; LCSC C7626

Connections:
/+3V3: R31.2, R32.2; also elsewhere on the board
/+5V_LOGIC: C12.1, C13.1, C16.1, U4.20 (VCC), U5.20 (VCC), U8.20 (VCC); also elsewhere on the board
/CAD0: U4.18 (B1); also elsewhere on the board
/CAD1: U4.17 (B2); also elsewhere on the board
/CAD2: U4.16 (B3); also elsewhere on the board
/CAD3: U4.15 (B4); also elsewhere on the board
/CAD4: U4.14 (B5); also elsewhere on the board
/CAD5: U4.13 (B6); also elsewhere on the board
/CAD6: U4.12 (B7); also elsewhere on the board
/CAD7: U4.11 (B8); also elsewhere on the board
/CART_RD_N: TP18.1, U8.16 (Y3); also elsewhere on the board
/CART_WR_N: TP19.1; also elsewhere on the board
/GND: C12.2, C13.2, C16.2, U4.10 (GND), U5.10 (GND), U8.5 (A4), U8.6 (A5), U8.7 (A6), U8.8 (A7), U8.9 (A8), U8.10 (GND); also elsewhere on the board
/GPA13: U8.3 (A2); also elsewhere on the board
/G_M2_N: R31.1, U4.19 (OE_N), U8.2 (A1); also elsewhere on the board
/G_RD: U8.4 (A3); also elsewhere on the board
/G_RW: U4.1 (DIR); also elsewhere on the board
/G_WR_N: U5.1 (DIR); also elsewhere on the board
/M2_CART: U8.18 (Y1); also elsewhere on the board
/OUT_OE_N: U8.1 (OE1_N), U8.19 (OE2_N); also elsewhere on the board
/PA13_N: U8.17 (Y2); also elsewhere on the board
/PAD0: U5.18 (B1); also elsewhere on the board
/PAD1: U5.17 (B2); also elsewhere on the board
/PAD2: U5.16 (B3); also elsewhere on the board
/PAD3: U5.15 (B4); also elsewhere on the board
/PAD4: U5.14 (B5); also elsewhere on the board
/PAD5: U5.13 (B6); also elsewhere on the board
/PAD6: U5.12 (B7); also elsewhere on the board
/PAD7: U5.11 (B8); also elsewhere on the board
/PPU_DEN_N: R32.1, TP16.1, U5.19 (OE_N); also elsewhere on the board
/XCD0: TP4.1, U4.2 (A1); also elsewhere on the board
/XCD1: U4.3 (A2); also elsewhere on the board
/XCD2: U4.4 (A3); also elsewhere on the board
/XCD3: U4.5 (A4); also elsewhere on the board
/XCD4: U4.6 (A5); also elsewhere on the board
/XCD5: U4.7 (A6); also elsewhere on the board
/XCD6: U4.8 (A7); also elsewhere on the board
/XCD7: U4.9 (A8); also elsewhere on the board
/XPD0: TP20.1, U5.2 (A1); also elsewhere on the board
/XPD1: U5.3 (A2); also elsewhere on the board
/XPD2: U5.4 (A3); also elsewhere on the board
/XPD3: U5.5 (A4); also elsewhere on the board
/XPD4: U5.6 (A5); also elsewhere on the board
/XPD5: U5.7 (A6); also elsewhere on the board
/XPD6: U5.8 (A7); also elsewhere on the board
/XPD7: U5.9 (A8); also elsewhere on the board

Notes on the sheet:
CPU data transceiver (74AHCT245)
PPU data transceiver (74AHCT245)
Control decoder / inverter (74AHCT540)
Decoupling U4/U5/U8
Enable pull-ups
Test points

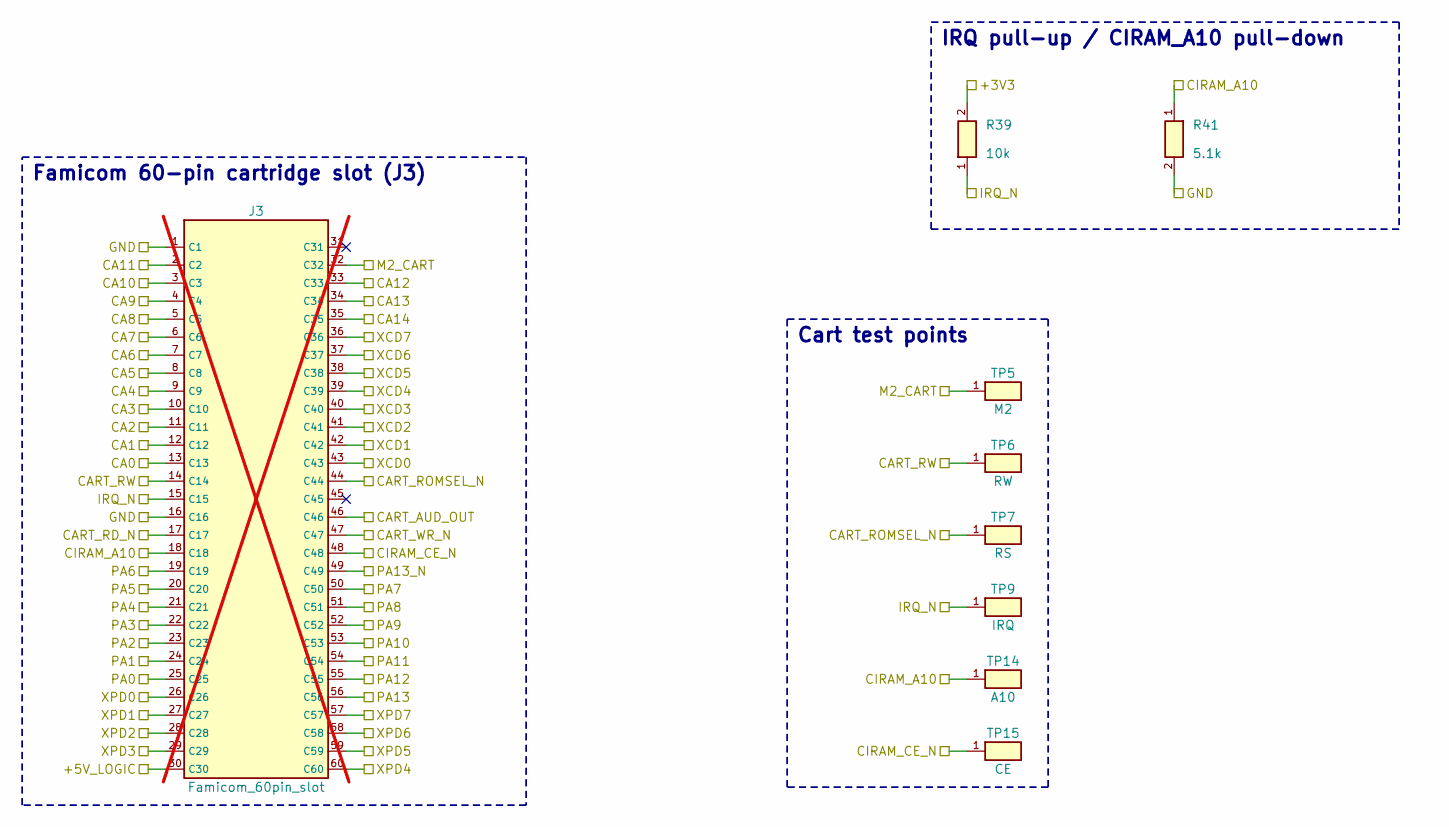
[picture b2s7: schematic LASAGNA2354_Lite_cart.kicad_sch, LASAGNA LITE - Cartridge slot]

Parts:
J3: Famicom_60pin_slot; Hirose_CR22A-60D-2.54DS; MPN CR22A-60D-2.54DS(70); LCSC_Status hand-assembly / not PCBA; not fitted
R39: 10k; R_0603_1608Metric; MPN 10k; LCSC C25804
R41: 5.1k; R_0603_1608Metric; MPN 5.1k; LCSC C23186
TP5: M2; TestPoint_THTPad_D2.0mm_Drill1.0mm; LCSC_Status no LCSC part
TP6: RW; TestPoint_THTPad_D2.0mm_Drill1.0mm; LCSC_Status no LCSC part
TP7: RS; TestPoint_THTPad_D2.0mm_Drill1.0mm; LCSC_Status no LCSC part
TP9: IRQ; TestPoint_THTPad_D2.0mm_Drill1.0mm; LCSC_Status no LCSC part
TP14: A10; TestPoint_THTPad_D2.0mm_Drill1.0mm; LCSC_Status no LCSC part
TP15: CE; TestPoint_THTPad_D2.0mm_Drill1.0mm; LCSC_Status no LCSC part

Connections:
/+3V3: R39.2; also elsewhere on the board
/+5V_LOGIC: J3.30 (C30); also elsewhere on the board
/CA0: J3.13 (C13); also elsewhere on the board
/CA1: J3.12 (C12); also elsewhere on the board
/CA2: J3.11 (C11); also elsewhere on the board
/CA3: J3.10 (C10); also elsewhere on the board
/CA4: J3.9 (C9); also elsewhere on the board
/CA5: J3.8 (C8); also elsewhere on the board
/CA6: J3.7 (C7); also elsewhere on the board
/CA7: J3.6 (C6); also elsewhere on the board
/CA8: J3.5 (C5); also elsewhere on the board
/CA9: J3.4 (C4); also elsewhere on the board
/CA10: J3.3 (C3); also elsewhere on the board
/CA11: J3.2 (C2); also elsewhere on the board
/CA12: J3.33 (C33); also elsewhere on the board
/CA13: J3.34 (C34); also elsewhere on the board
/CA14: J3.35 (C35); also elsewhere on the board
/CART_AUD_OUT: J3.46 (C46); also elsewhere on the board
/CART_RD_N: J3.17 (C17); also elsewhere on the board
/CART_ROMSEL_N: J3.44 (C44), TP7.1; also elsewhere on the board
/CART_RW: J3.14 (C14), TP6.1; also elsewhere on the board
/CART_WR_N: J3.47 (C47); also elsewhere on the board
/CIRAM_A10: J3.18 (C18), R41.1, TP14.1; also elsewhere on the board
/CIRAM_CE_N: J3.48 (C48), TP15.1; also elsewhere on the board
/GND: J3.1 (C1), J3.16 (C16), R41.2; also elsewhere on the board
/IRQ_N: J3.15 (C15), R39.1, TP9.1; also elsewhere on the board
/M2_CART: J3.32 (C32), TP5.1; also elsewhere on the board
/PA0: J3.25 (C25); also elsewhere on the board
/PA1: J3.24 (C24); also elsewhere on the board
/PA2: J3.23 (C23); also elsewhere on the board
/PA3: J3.22 (C22); also elsewhere on the board
/PA4: J3.21 (C21); also elsewhere on the board
/PA5: J3.20 (C20); also elsewhere on the board
/PA6: J3.19 (C19); also elsewhere on the board
/PA7: J3.50 (C50); also elsewhere on the board
/PA8: J3.51 (C51); also elsewhere on the board
/PA9: J3.52 (C52); also elsewhere on the board
/PA10: J3.53 (C53); also elsewhere on the board
/PA11: J3.54 (C54); also elsewhere on the board
/PA12: J3.55 (C55); also elsewhere on the board
/PA13: J3.56 (C56); also elsewhere on the board
/PA13_N: J3.49 (C49); also elsewhere on the board
/XCD0: J3.43 (C43); also elsewhere on the board
/XCD1: J3.42 (C42); also elsewhere on the board
/XCD2: J3.41 (C41); also elsewhere on the board
/XCD3: J3.40 (C40); also elsewhere on the board
/XCD4: J3.39 (C39); also elsewhere on the board
/XCD5: J3.38 (C38); also elsewhere on the board
/XCD6: J3.37 (C37); also elsewhere on the board
/XCD7: J3.36 (C36); also elsewhere on the board
/XPD0: J3.26 (C26); also elsewhere on the board
/XPD1: J3.27 (C27); also elsewhere on the board
/XPD2: J3.28 (C28); also elsewhere on the board
/XPD3: J3.29 (C29); also elsewhere on the board
/XPD4: J3.60 (C60); also elsewhere on the board
/XPD5: J3.59 (C59); also elsewhere on the board
/XPD6: J3.58 (C58); also elsewhere on the board
/XPD7: J3.57 (C57); also elsewhere on the board

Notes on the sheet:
Famicom 60-pin cartridge slot (J3)
IRQ pull-up / CIRAM_A10 pull-down
Cart test points
